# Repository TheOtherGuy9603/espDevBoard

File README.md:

View this project on [CADLAB.io](https://cadlab.io/project/1111). 

# espDevBoard
a development board using esp8266-12e (untested)

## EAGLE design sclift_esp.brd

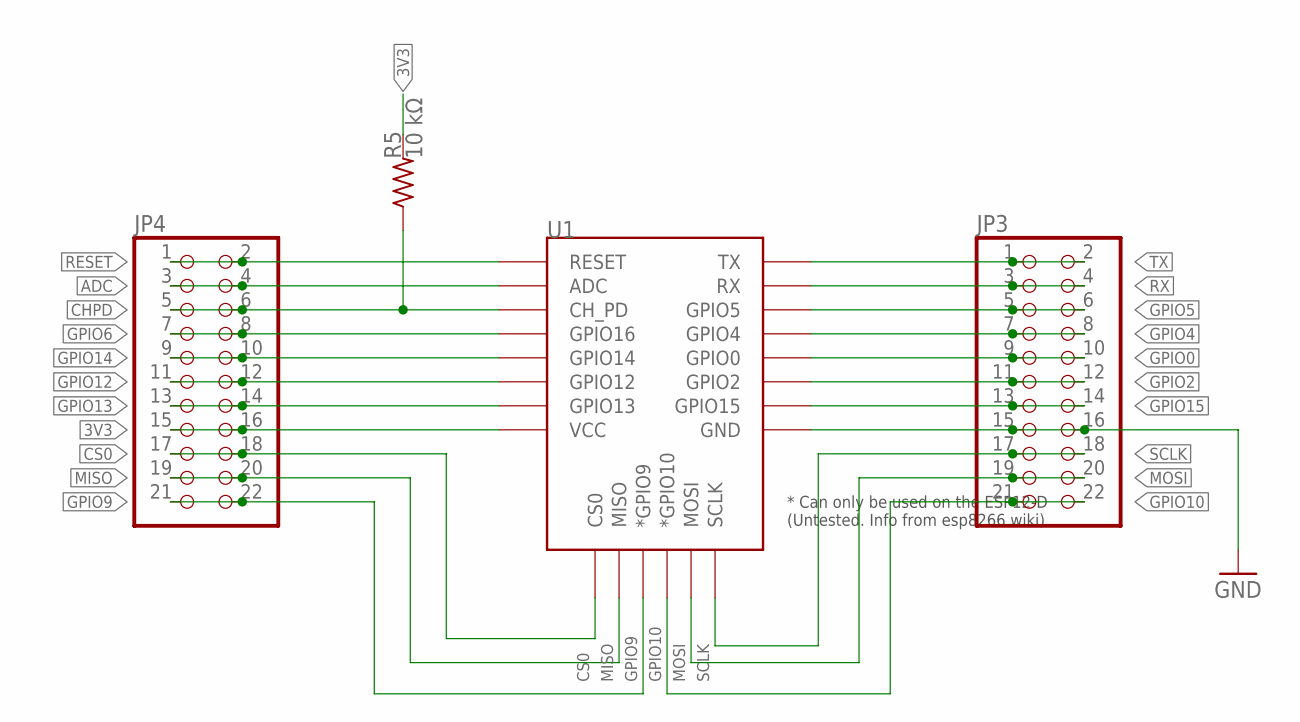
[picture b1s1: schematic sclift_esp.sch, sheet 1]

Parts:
JP3, JP4: PINHD-2X11; 2X11
R5: 10 kΩ; 0204/7
U1: ESP12ESMD; ESP12E-SMD

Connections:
3V3: JP4.15, JP4.16, R5.2, U1.VCC; also elsewhere on the board
ADC: JP4.3, JP4.4, U1.ADC
CHPD: JP4.5, JP4.6, R5.1, U1.CH_PD
CS0: JP4.17, JP4.18, U1.CS0
GND: JP3.15, JP3.16, U1.GND; also elsewhere on the board
GPIO0: JP3.9, JP3.10, U1.GPIO0; also elsewhere on the board
GPIO2: JP3.11, JP3.12, U1.GPIO2; also elsewhere on the board
GPIO4: JP3.7, JP3.8, U1.GPIO4
GPIO5: JP3.5, JP3.6, U1.GPIO5
GPIO6: JP4.7, JP4.8, U1.GPIO16
GPIO9: JP4.21, JP4.22, U1.GPIO9 (*GPIO9)
GPIO10: JP3.21, JP3.22, U1.GPIO10 (*GPIO10)
GPIO12: JP4.11, JP4.12, U1.GPIO12
GPIO13: JP4.13, JP4.14, U1.GPIO13
GPIO14: JP4.9, JP4.10, U1.GPIO14
GPIO15: JP3.13, JP3.14, U1.GPIO15; also elsewhere on the board
MISO: JP4.19, JP4.20, U1.MISO
MOSI: JP3.19, JP3.20, U1.MOSI
RESET: JP4.1, JP4.2, U1.RESET; also elsewhere on the board
RX: JP3.3, JP3.4, U1.RXD0 (RX); also elsewhere on the board
SCLK: JP3.17, JP3.18, U1.SCLK
TX: JP3.1, JP3.2, U1.TXD0 (TX); also elsewhere on the board

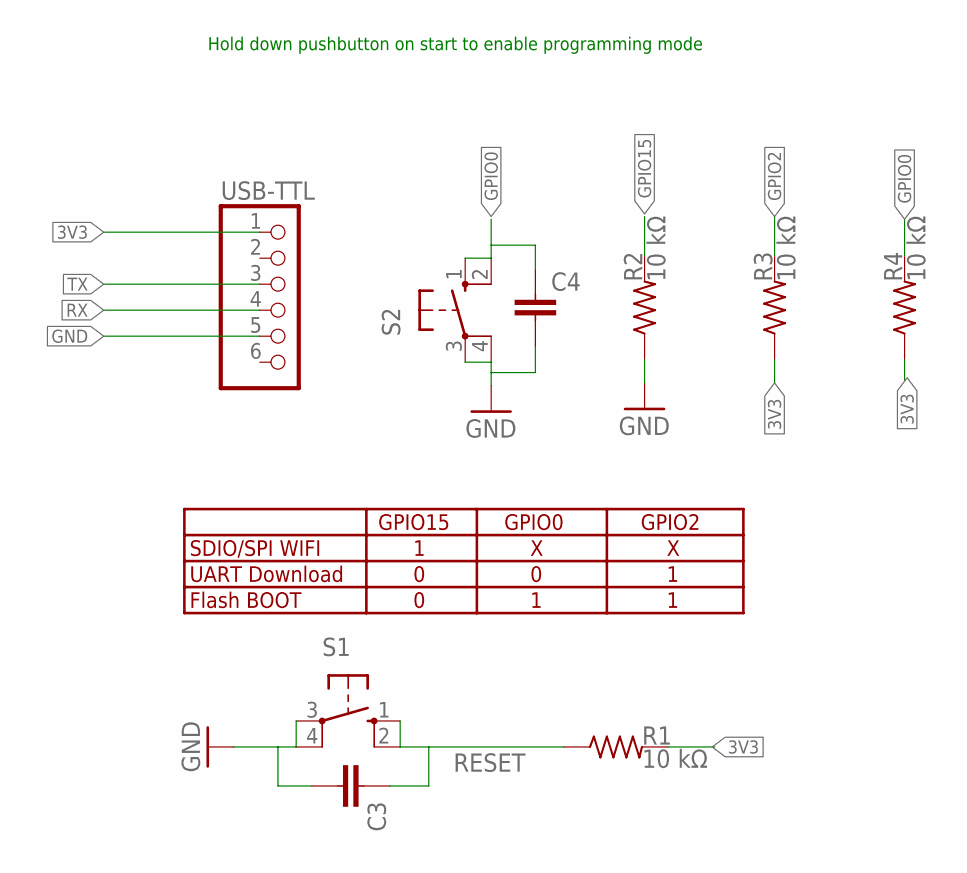
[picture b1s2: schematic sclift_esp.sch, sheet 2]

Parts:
C3, C4: C-EU025-024X044; C025-024X044
R1, R2, R3, R4: 10 kΩ; 0204/7
S1, S2: 10-XX; B3F-10XX
USB-TTL: PINHD-1X6; 1X06

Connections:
3V3: R1.2, R3.1, R4.1, USB-TTL.1; also elsewhere on the board
GND: C3.2, C4.2, R2.1, S1.3, S1.4 (P1), S2.3, S2.4 (P1), USB-TTL.5; also elsewhere on the board
GPIO0: C4.1, R4.2, S2.1 (S), S2.2 (S1); also elsewhere on the board
GPIO2: R3.2; also elsewhere on the board
GPIO15: R2.2; also elsewhere on the board
RESET: C3.1, R1.1, S1.1 (S), S1.2 (S1); also elsewhere on the board
RX: USB-TTL.4; also elsewhere on the board
TX: USB-TTL.3; also elsewhere on the board

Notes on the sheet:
SDIO/SPI WIFI
UART Download
Flash BOOT
GPIO15
GPIO0
GPIO2
Hold down pushbutton on start to enable programming mode

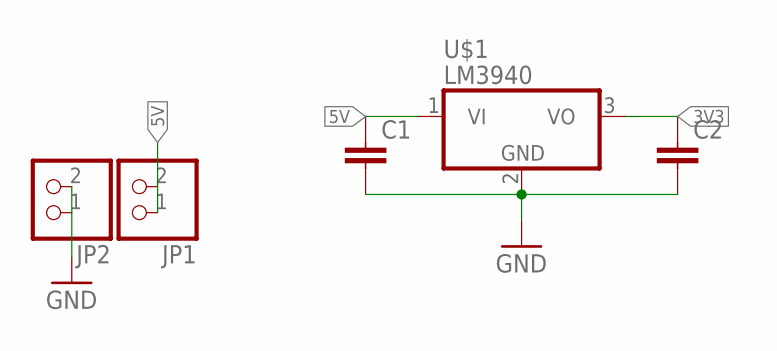
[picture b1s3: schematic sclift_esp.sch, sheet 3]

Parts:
C1, C2: C-EU025-024X044; C025-024X044
JP1, JP2: PINHD-1X2; 1X02
U$1: LM3940; TO220H

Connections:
3V3: C2.1, U$1.3 (VO); also elsewhere on the board
5V: C1.1, JP1.1, JP1.2, U$1.1 (VI)
GND: C1.2, C2.2, JP2.1, JP2.2, U$1.2 (GND); also elsewhere on the board

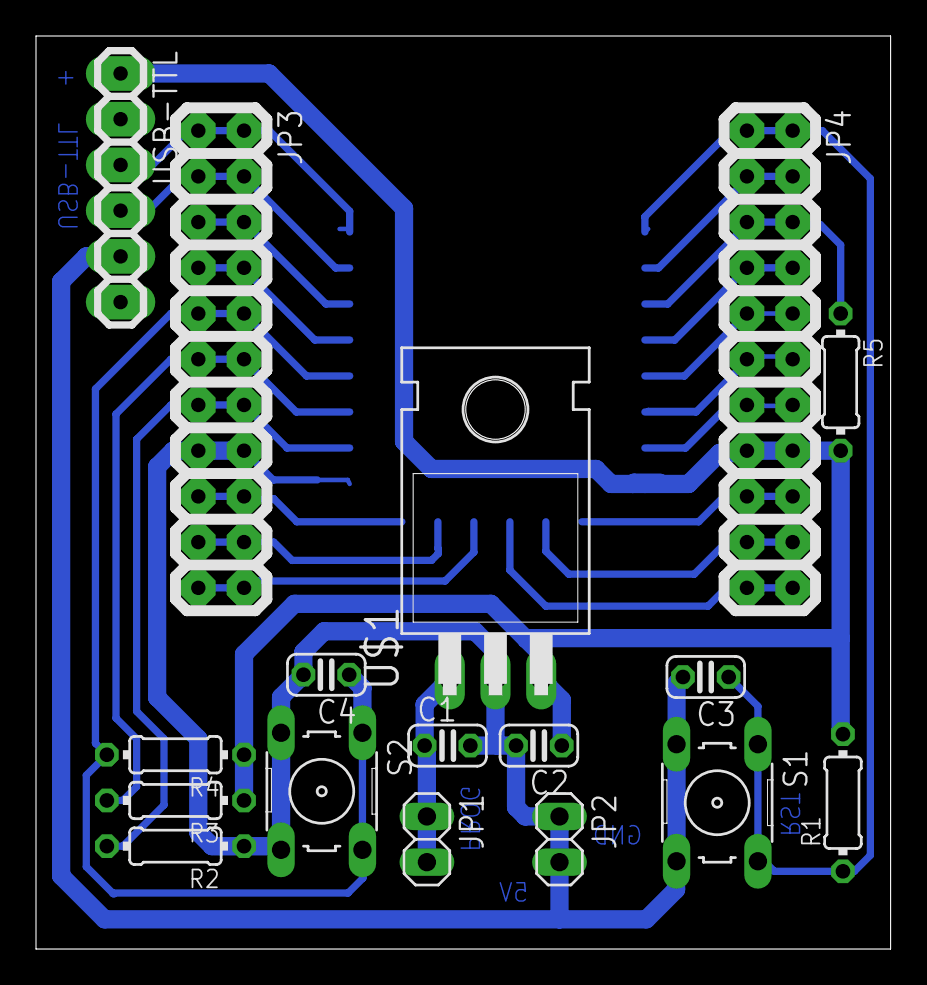
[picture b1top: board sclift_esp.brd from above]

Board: 2 copper layers, 47.5 x 50.7 mm, 18 parts (1 on the bottom side), 23 nets.

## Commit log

2018-05-30 Backlink to CADLAB.io has been added.
